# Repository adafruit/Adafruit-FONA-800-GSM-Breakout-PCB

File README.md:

# Adafruit FONA 800 GSM Breakout PCBs
&nbsp; <br />
Click to purchase from the Adafruit Shop:
- [Adafruit FONA - Mini Cellular GSM Breakout - SMA Version - v1](https://www.adafruit.com/product/1963)
- [Adafruit FONA - Mini Cellular GSM Breakout uFL Version](https://www.adafruit.com/product/1946)

This module measures only 1.75"x1.25" but packs a surprising amount of technology into its little frame. At the heart is a GSM cellular module (we use the latest SIM800) the size of a postage stamp. This module can do just about everything. One version has an SMA connector, the other has a uFL connector.

Quad-band 850/900/1800/1900MHz - connect onto any global GSM network with any 2G SIM (in the USA, T-Mobile is suggested)
- Make and receive voice calls using a headset OR an external 8Ω speaker + electret microphone
- Send and receive SMS messages
- Send and receive GPRS data (TCP/IP, HTTP, etc.)
- Scan and receive FM radio broadcasts (yeah, we don't exactly know why this was included but it works really well)
- PWM/Buzzer vibrational motor control
- AT command interface with "auto baud" detection

PCB files for the Adafruit FONA 800 GSM Cellular Breakouts. The format is EagleCAD schematic and board layout
- https://www.adafruit.com/products/1963
- https://www.adafruit.com/products/1946

### License

Adafruit invests time and resources providing this open source design, please support Adafruit and open-source hardware by purchasing products from [Adafruit](https://www.adafruit.com)!

All text above must be included in any redistribution

Designed by Limor Fried/Ladyada for Adafruit Industries.
Creative Commons Attribution/Share-Alike, all text above must be included in any redistribution. 
See license.txt for additional information.

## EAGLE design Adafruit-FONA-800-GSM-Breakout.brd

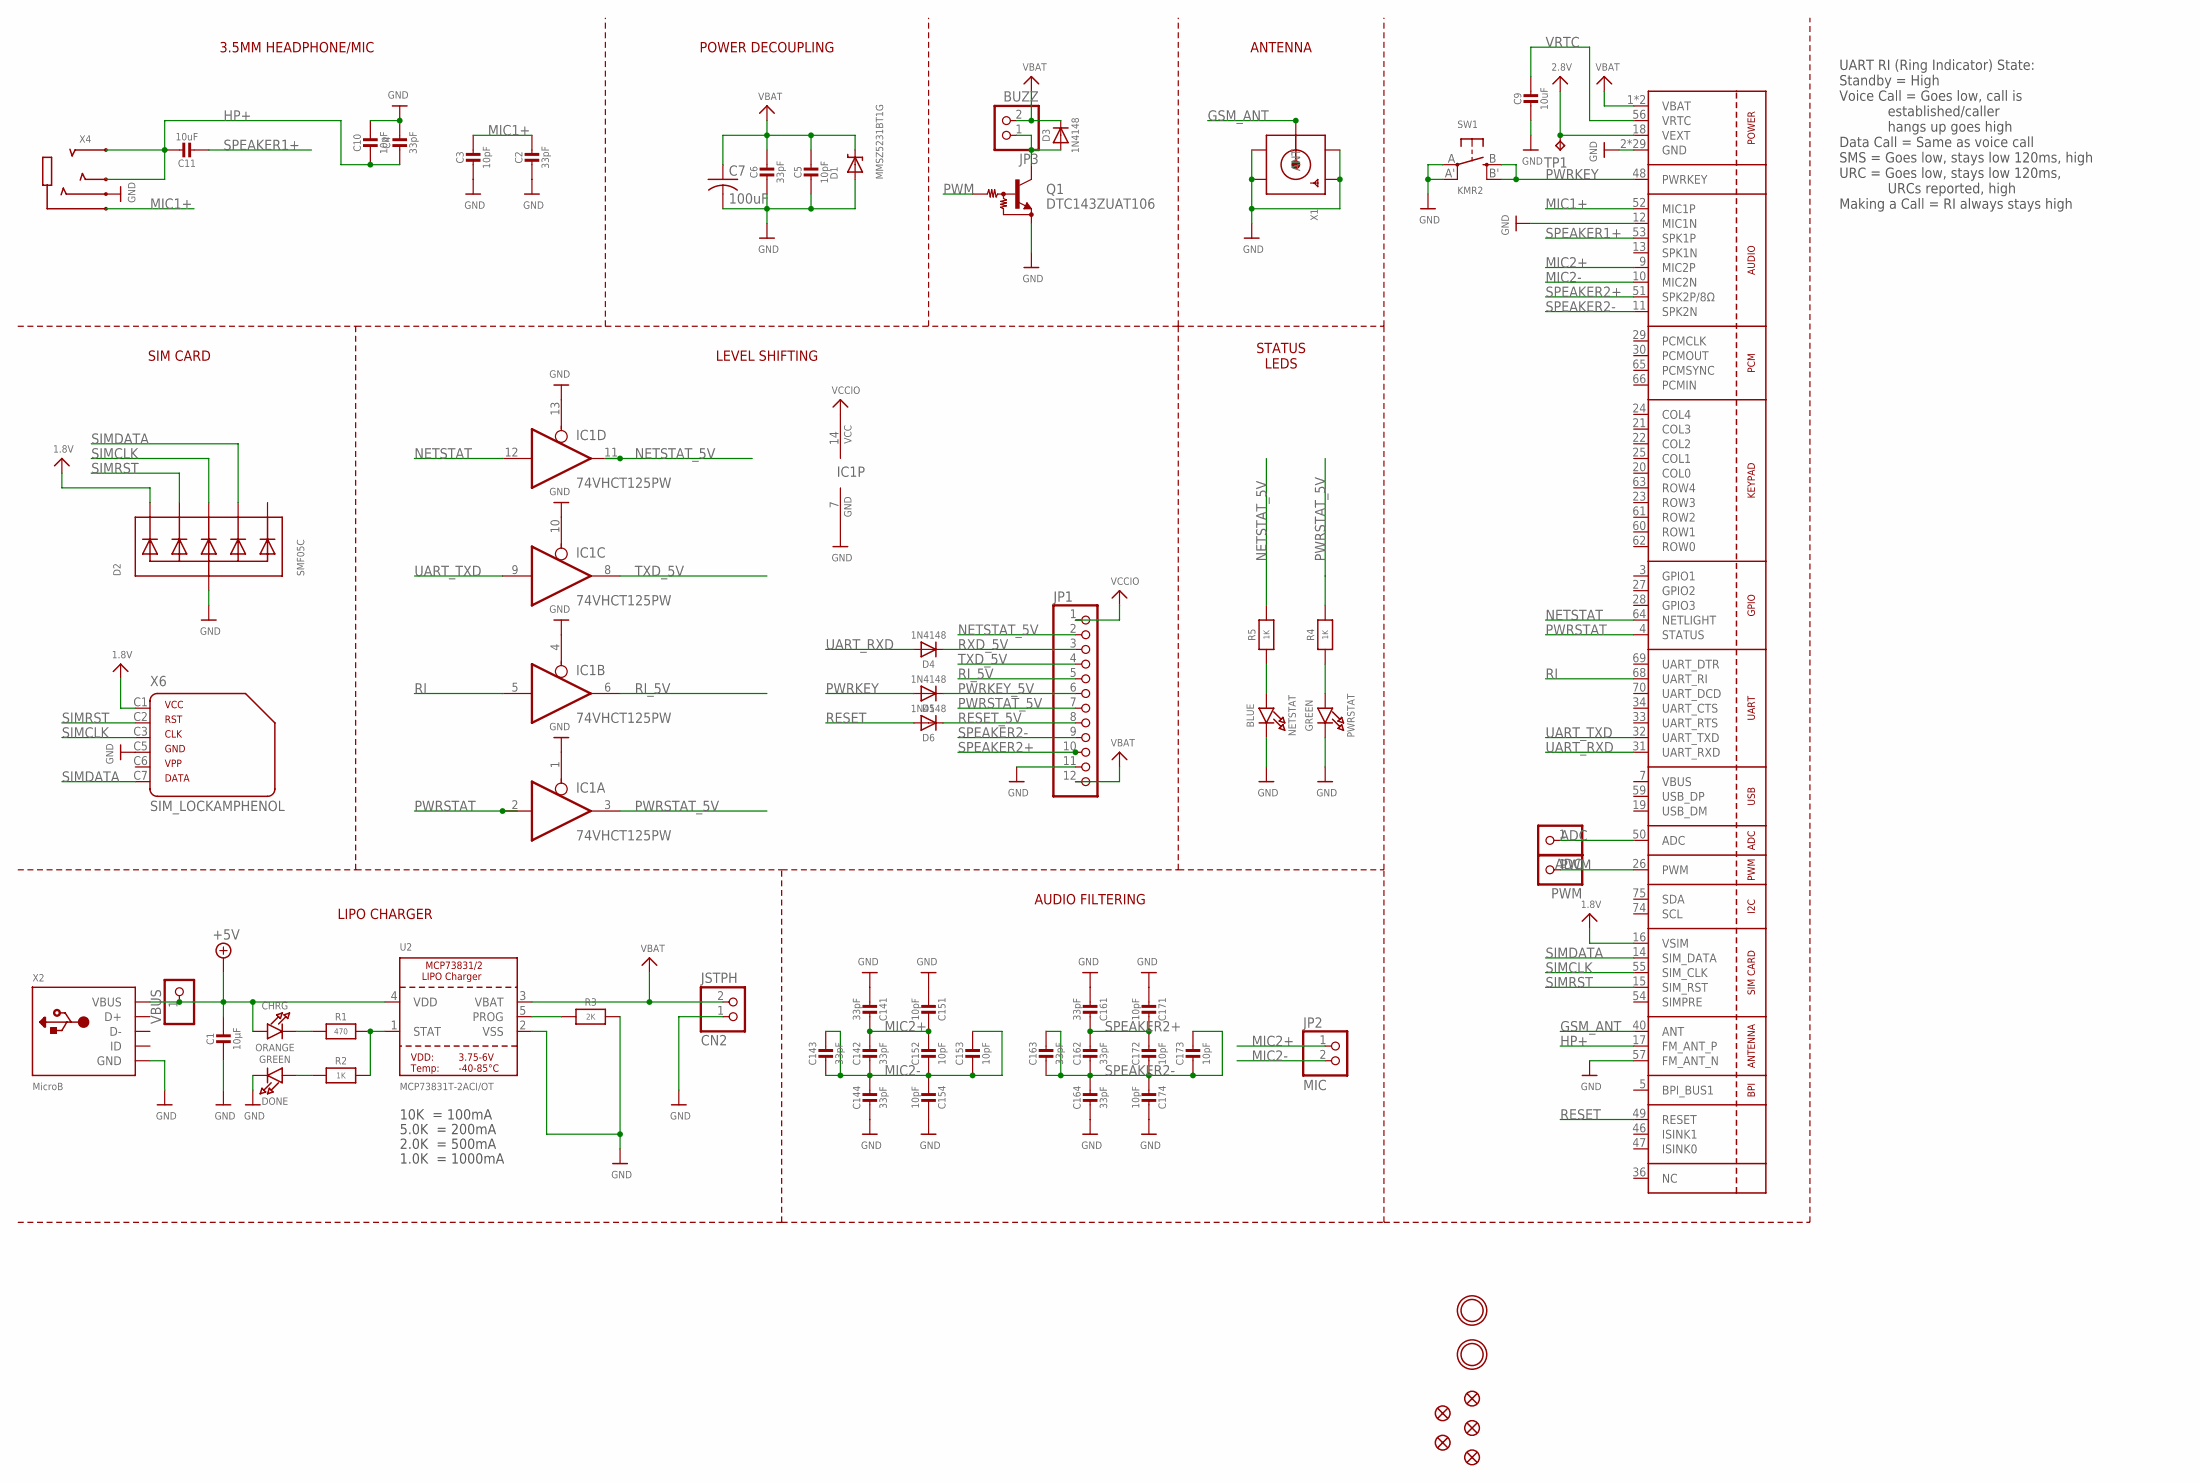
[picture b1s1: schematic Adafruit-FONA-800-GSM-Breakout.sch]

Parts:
ADC: PINHD-1X1CB; 1X01-CLEANBIG
C1: 10µF; 0805-NO
C2, C4, C6: 33pF; 0805-NO
C3, C5, C10: 10pF; 0805-NO
C7: 100uF; C1210
C9, C11: 10uF; 0805-NO
C14, C16: 33pF; RESPACK_4X0603
C15, C17: 10pF; RESPACK_4X0603
CHRG: ORANGE; CHIPLED_0805_NOOUTLINE
CN2: JSTPH; JSTPH2
D1: MMSZ5231BT1G; SOD-123
D2: SMF05C; SOT363
D3, D4, D5, D6: 1N4148; SOD-323
DONE: GREEN; CHIPLED_0805_NOOUTLINE
FID1, FID2, FID3, FID4, FID5: FIDUCIAL""; FIDUCIAL_1MM
IC1: 74VHCT125PW; TSSOP14
JP1: PINHD-1X12-CB; 1X12-CB
JP2: MIC; 1X02_ROUND
JP3: BUZZ; 1X02_ROUND
NETSTAT: BLUE; CHIPLED_0805_NOOUTLINE
PWM: PINHD-1X1CB; 1X01-CLEANBIG
PWRSTAT: GREEN; CHIPLED_0805_NOOUTLINE
Q1: DTC143ZUAT106; SC59-BEC
R1: 470; 0805-NO
R2, R4, R5: 1K; 0805-NO
R3: 2K; 0805-NO
SW1: KMR2; BTN_KMR2_4.6X2.8
TP1: TPTP11R; TP11R
U1: SIM800H/L; SIM800L
U2: MCP73831T-2ACI/OT; SOT23-5
U$33, U$34: MOUNTINGHOLE2.5; MOUNTINGHOLE_2.5_PLATED
VBUS: PINHD-1X1CB; 1X01-CLEANBIG
X1: SMACONNECTOR_EDGE_UFL; SMA_EDGELAUNCH_UFL
X2: MicroB; 4UCONN_20329
X4: AUDIO_3.5MMJACK_4POL; 4UCONN_18510
X6: SIM_LOCKAMPHENOL; C707_10M006_512_2

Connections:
1.8V: D2.1 (C1), U1.16 (VSIM), X6.C1 (1)
2.8V: TP1.TP, U1.18 (VEXT)
+5V: C1.1, CHRG.A, U2.4 (VDD), VBUS.1, X2.VBUS
ADC: ADC.1, U1.50 (ADC)
GND: C1.2, C2.2, C3.2, C4.1, C5.2, C6.2, C7.2, C9.2, C10.1, C14.5 (2), C14.8 (2), C15.4 (1), C15.8 (2), C16.5 (2), C16.8 (2), C17.4 (1), C17.8 (2), CN2.1, D1.A, D2.2 (A), DONE.C, IC1.1 (OE), IC1.4 (OE), IC1.7 (GND), IC1.10 (OE), IC1.13 (OE), JP1.11, NETSTAT.C, PWRSTAT.C, Q1.E, R3.2, SW1.A, SW1.A' (P1), U1.2 (GND), U1.6 (GND), U1.8 (GND), U1.12 (MIC1N), U1.35 (GND), U1.37 (GND), U1.38 (GND), U1.39 (GND), U1.41 (GND), U1.43 (GND), U1.44 (GND), U1.45 (GND), U1.57 (FM_ANT_N), U1.58 (GND), U1.67 (GND), U1.71 (GND), U1.72 (GND), U1.73 (GND), U1.76 (GND), U1.77 (GND), U1.78 (GND), U1.79 (GND), U1.80 (GND), U1.81 (GND), U1.82 (GND), U1.83 (GND), U1.84 (GND), U1.85 (GND), U1.86 (GND), U1.87 (GND), U1.88 (GND), U2.2 (VSS), X1.GND@1 (GND1), X1.GND@2 (GND2), X1.GND@3 (GND3), X1.GND@4 (GND4), X2.BASE@1 (GND), X2.BASE@2 (GND), X2.GND, X2.SPRT@1 (GND), X2.SPRT@2 (GND), X2.SPRT@3 (GND), X2.SPRT@4 (GND), X4.4-INNER_SLEEVE (RING1), X6.C5 (4)
GSM_ANT: U1.40 (ANT), X1.P (ANT)
HP+: C4.2, C10.2, C11.1, U1.17 (FM_ANT_P), X4.2-TIP (RING3), X4.3-OUTER_SLEEVE (RING2)
MIC1+: C2.1, C3.1, U1.52 (MIC1P), X4.1-GND (TIP)
MIC2+: C14.1, C14.2 (1), C15.1, C15.2 (1), JP2.1, U1.9 (MIC2P)
MIC2-: C14.3 (1), C14.4 (1), C14.6 (2), C14.7 (2), C15.3 (1), C15.5 (2), C15.6 (2), C15.7 (2), JP2.2, U1.10 (MIC2N)
unnamed: CHRG.C, R1.1
unnamed: R1.2, R2.2, U2.1 (STAT)
unnamed: PWRSTAT.A, R4.1
unnamed: R3.1, U2.5 (PROG)
unnamed: DONE.A, R2.1
unnamed: NETSTAT.A, R5.1
unnamed: D3.A, JP3.1, Q1.C
NETSTAT: IC1.12 (I), U1.64 (NETLIGHT)
NETSTAT_5V: IC1.11 (O), JP1.2, R5.2
PWM: PWM.1, Q1.B, U1.26 (PWM)
PWRKEY: D5.A, SW1.B (S), SW1.B' (S1), U1.48 (PWRKEY)
PWRKEY_5V: D5.C, JP1.6
PWRSTAT: IC1.2 (I), U1.4 (STATUS)
PWRSTAT_5V: IC1.3 (O), JP1.7, R4.2
RESET: D6.A, U1.49 (RESET)
RESET_5V: D6.C, JP1.8
RI: IC1.5 (I), U1.68 (UART_RI)
RI_5V: IC1.6 (O), JP1.5
RXD_5V: D4.C, JP1.3
SIMCLK: D2.4 (C3), U1.55 (SIM_CLK), X6.C3 (3)
SIMDATA: D2.5 (C4), U1.14 (SIM_DATA), X6.C7 (6)
SIMRST: D2.3 (C2), U1.15 (SIM_RST), X6.C2 (2)
SPEAKER1+: C11.2, U1.53 (SPK1P)
SPEAKER2+: C16.1, C16.2 (1), C17.1, C17.2 (1), JP1.10, U1.51 (SPK2P/8Ω)
SPEAKER2-: C16.3 (1), C16.4 (1), C16.6 (2), C16.7 (2), C17.3 (1), C17.5 (2), C17.6 (2), C17.7 (2), JP1.9, U1.11 (SPK2N)
TXD_5V: IC1.8 (O), JP1.4
UART_RXD: D4.A, U1.31 (UART_RXD)
UART_TXD: IC1.9 (I), U1.32 (UART_TXD)
VBAT: C5.1, C6.1, C7.1, CN2.2, D1.C, D3.C, JP1.12, JP3.2, U1.1 (VBAT), U1.42 (VBAT), U2.3 (VBAT)
VBUS: U1.7 (VBUS)
VCCIO: IC1.14 (VCC), JP1.1
VRTC: C9.1, U1.56 (VRTC)

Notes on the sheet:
10K = 100mA
5.0K = 200mA
2.0K = 500mA
1.0K = 1000mA
UART RI (Ring Indicator) State: Standby = High Voice Call = Goes low, call is established/caller hangs up goes high Data Call = Same as voice call SMS = Goes low, stays low 120ms, high URC = Goes low, stays low 120ms, URCs reported, high Making a Call = RI always stays high
ANTENNA
POWER DECOUPLING
3.5MM HEADPHONE/MIC
SIM CARD
LEVEL SHIFTING
LIPO CHARGER
AUDIO FILTERING
STATUS LEDS

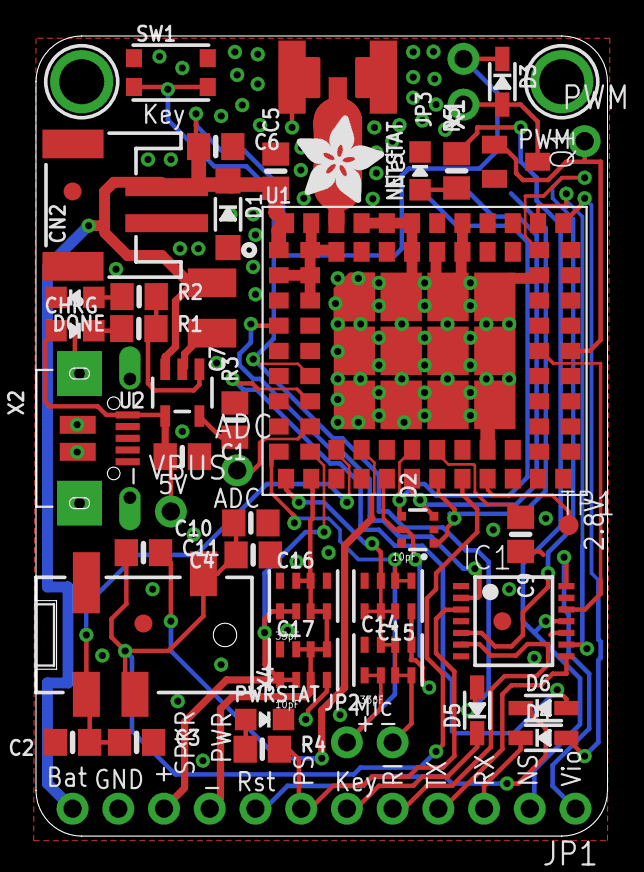
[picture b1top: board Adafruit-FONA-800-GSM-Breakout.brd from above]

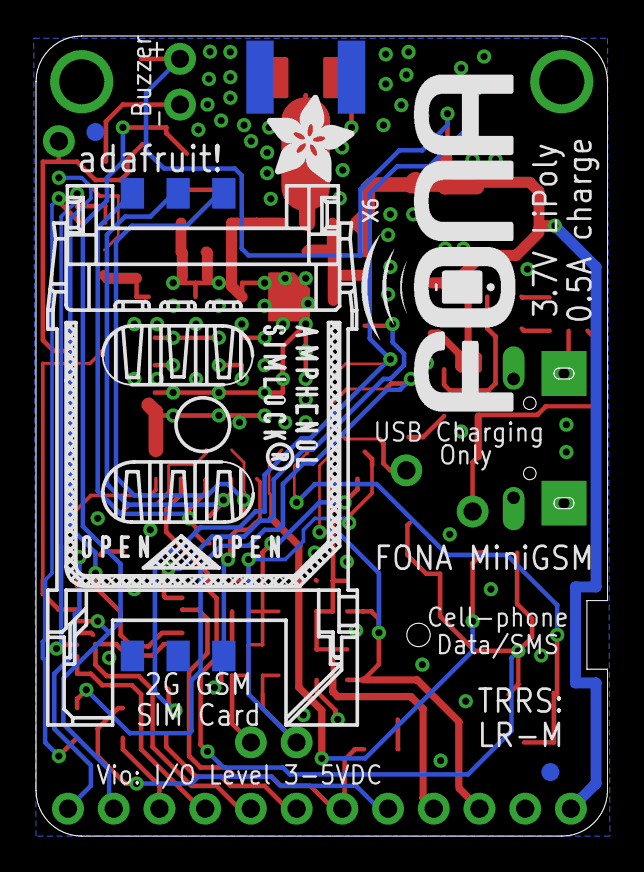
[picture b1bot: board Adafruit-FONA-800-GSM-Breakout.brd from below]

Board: 2 copper layers, 31.8 x 44.5 mm, 56 parts (5 on the bottom side), 41 nets.

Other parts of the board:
U$10, U$36: ADAFRUIT_5MM
U$26: FONA_LOGO

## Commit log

2015-03-10 pcb files
2015-03-10 urls

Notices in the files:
parts and their libraries:
microbuilder: This work is placed in the public domain, and may be freely used for commercial and non-commercial work with the following conditions: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
